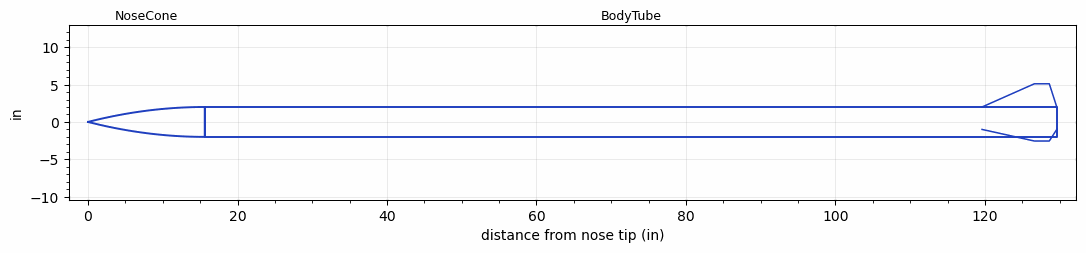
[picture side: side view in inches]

<RASAeroDocument>
 <FileVersion>2</FileVersion>
 <RocketDesign>
  <NoseCone>
   <Length>15.616</Length>
   <Diameter>4</Diameter>
   <Shape>Parabolic</Shape>
   <BluntRadius>0.1</BluntRadius>
   <Location>0</Location>
  </NoseCone>
  <BodyTube>
   <Length>114</Length>
   <Diameter>4</Diameter>
   <Location>15.616</Location>
   <Fin>
    <Count>3</Count>
    <Chord>10</Chord>
    <Span>3.105</Span>
    <SweepDistance>7</SweepDistance>
    <TipChord>2</TipChord>
    <Thickness>0.25</Thickness>
    <LERadius>0.125</LERadius>
    <Location>10</Location>
    <AirfoilSection>Double Wedge</AirfoilSection>
    <FX1>1</FX1>
   </Fin>
  </BodyTube>
  <Surface>Rough Camouflage Paint</Surface>
  <ModifiedBarrowman>False</ModifiedBarrowman>
  <Turbulence>False</Turbulence>
  <UseBooster1>False</UseBooster1>
  <UseBooster2>False</UseBooster2>
 </RocketDesign>
 <LaunchSite>
  <Altitude>112</Altitude>
  <Pressure>0</Pressure>
  <RodAngle>7</RodAngle>
  <RodLength>10</RodLength>
  <Temperature>62</Temperature>
  <WindSpeed>2</WindSpeed>
 </LaunchSite>
 <Recovery>
  <Altitude1>1000</Altitude1>
  <Altitude2>1500</Altitude2>
  <DeviceType1>Parachute</DeviceType1>
  <DeviceType2>Parachute</DeviceType2>
  <Event1>True</Event1>
  <Event2>True</Event2>
  <Size1>30.57</Size1>
  <Size2>96</Size2>
  <EventType1>Apogee</EventType1>
  <EventType2>Altitude</EventType2>
  <CD1>0.75</CD1>
  <CD2>2.2</CD2>
 </Recovery>
 <SimulationList>
  <Simulation>
   <SustainerEngine>K1075-SK-P  (CTI)</SustainerEngine>
   <SustainerLaunchWt>24.2</SustainerLaunchWt>
   <SustainerNozzleDiameter>2</SustainerNozzleDiameter>
   <SustainerCG>75</SustainerCG>
   <SustainerIgnitionDelay>0</SustainerIgnitionDelay>
   <Booster1SeparationDelay>0</Booster1SeparationDelay>
   <Booster1IgnitionDelay>0</Booster1IgnitionDelay>
   <IncludeBooster1>False</IncludeBooster1>
   <Booster2Delay>0</Booster2Delay>
   <IncludeBooster2>False</IncludeBooster2>
   <TimetoApogee>17.63031</TimetoApogee>
   <MaxAltitude>4973.731</MaxAltitude>
   <MaxVelocity>627.4751</MaxVelocity>
  </Simulation>
  <Simulation>
   <SustainerEngine>K2000-VM-P  (CTI)</SustainerEngine>
   <SustainerLaunchWt>24.2</SustainerLaunchWt>
   <SustainerCG>75</SustainerCG>
   <SustainerIgnitionDelay>0</SustainerIgnitionDelay>
   <Booster1SeparationDelay>0</Booster1SeparationDelay>
   <Booster1IgnitionDelay>0</Booster1IgnitionDelay>
   <IncludeBooster1>False</IncludeBooster1>
   <Booster2Delay>0</Booster2Delay>
   <IncludeBooster2>False</IncludeBooster2>
   <TimetoApogee>17.63031</TimetoApogee>
   <MaxAltitude>5292.853</MaxAltitude>
   <MaxVelocity>684.861</MaxVelocity>
  </Simulation>
  <Simulation>
   <SustainerEngine>L1395-BS  (CTI)</SustainerEngine>
   <SustainerLaunchWt>39.6</SustainerLaunchWt>
   <SustainerNozzleDiameter>1</SustainerNozzleDiameter>
   <SustainerCG>63</SustainerCG>
   <SustainerIgnitionDelay>0</SustainerIgnitionDelay>
   <Booster1SeparationDelay>0</Booster1SeparationDelay>
   <Booster1IgnitionDelay>0</Booster1IgnitionDelay>
   <IncludeBooster1>False</IncludeBooster1>
   <Booster2Delay>0</Booster2Delay>
   <IncludeBooster2>False</IncludeBooster2>
   <TimetoApogee>23.43044</TimetoApogee>
   <MaxAltitude>8613.106</MaxAltitude>
   <MaxVelocity>818.1671</MaxVelocity>
  </Simulation>
  <Simulation>
   <SustainerEngine>M1230-IM  (CTI)</SustainerEngine>
   <SustainerLaunchWt>29.5</SustainerLaunchWt>
   <SustainerNozzleDiameter>1</SustainerNozzleDiameter>
   <SustainerCG>82</SustainerCG>
   <SustainerIgnitionDelay>0</SustainerIgnitionDelay>
   <Booster1SeparationDelay>0</Booster1SeparationDelay>
   <Booster1IgnitionDelay>0</Booster1IgnitionDelay>
   <IncludeBooster1>False</IncludeBooster1>
   <Booster2Delay>0</Booster2Delay>
   <IncludeBooster2>False</IncludeBooster2>
   <TimetoApogee>27.40053</TimetoApogee>
   <MaxAltitude>13249.17</MaxAltitude>
   <MaxVelocity>1191.028</MaxVelocity>
  </Simulation>
  <Simulation>
   <SustainerEngine>K735-SK-P  (CTI)</SustainerEngine>
   <SustainerLaunchWt>36</SustainerLaunchWt>
   <SustainerCG>57</SustainerCG>
   <SustainerIgnitionDelay>0</SustainerIgnitionDelay>
   <Booster1SeparationDelay>0</Booster1SeparationDelay>
   <Booster1IgnitionDelay>0</Booster1IgnitionDelay>
   <IncludeBooster1>False</IncludeBooster1>
   <Booster2Delay>0</Booster2Delay>
   <IncludeBooster2>False</IncludeBooster2>
   <TimetoApogee>11.99018</TimetoApogee>
   <MaxAltitude>1855.363</MaxAltitude>
   <MaxVelocity>321.066</MaxVelocity>
  </Simulation>
  <Simulation>
   <SustainerEngine>K661-BS-P  (CTI)</SustainerEngine>
   <SustainerLaunchWt>35.6</SustainerLaunchWt>
   <SustainerCG>57</SustainerCG>
   <SustainerIgnitionDelay>0</SustainerIgnitionDelay>
   <Booster1SeparationDelay>0</Booster1SeparationDelay>
   <Booster1IgnitionDelay>0</Booster1IgnitionDelay>
   <IncludeBooster1>False</IncludeBooster1>
   <Booster2Delay>0</Booster2Delay>
   <IncludeBooster2>False</IncludeBooster2>
   <TimetoApogee>14.70024</TimetoApogee>
   <MaxAltitude>2752.566</MaxAltitude>
   <MaxVelocity>390.2598</MaxVelocity>
  </Simulation>
 </SimulationList>
</RASAeroDocument>
